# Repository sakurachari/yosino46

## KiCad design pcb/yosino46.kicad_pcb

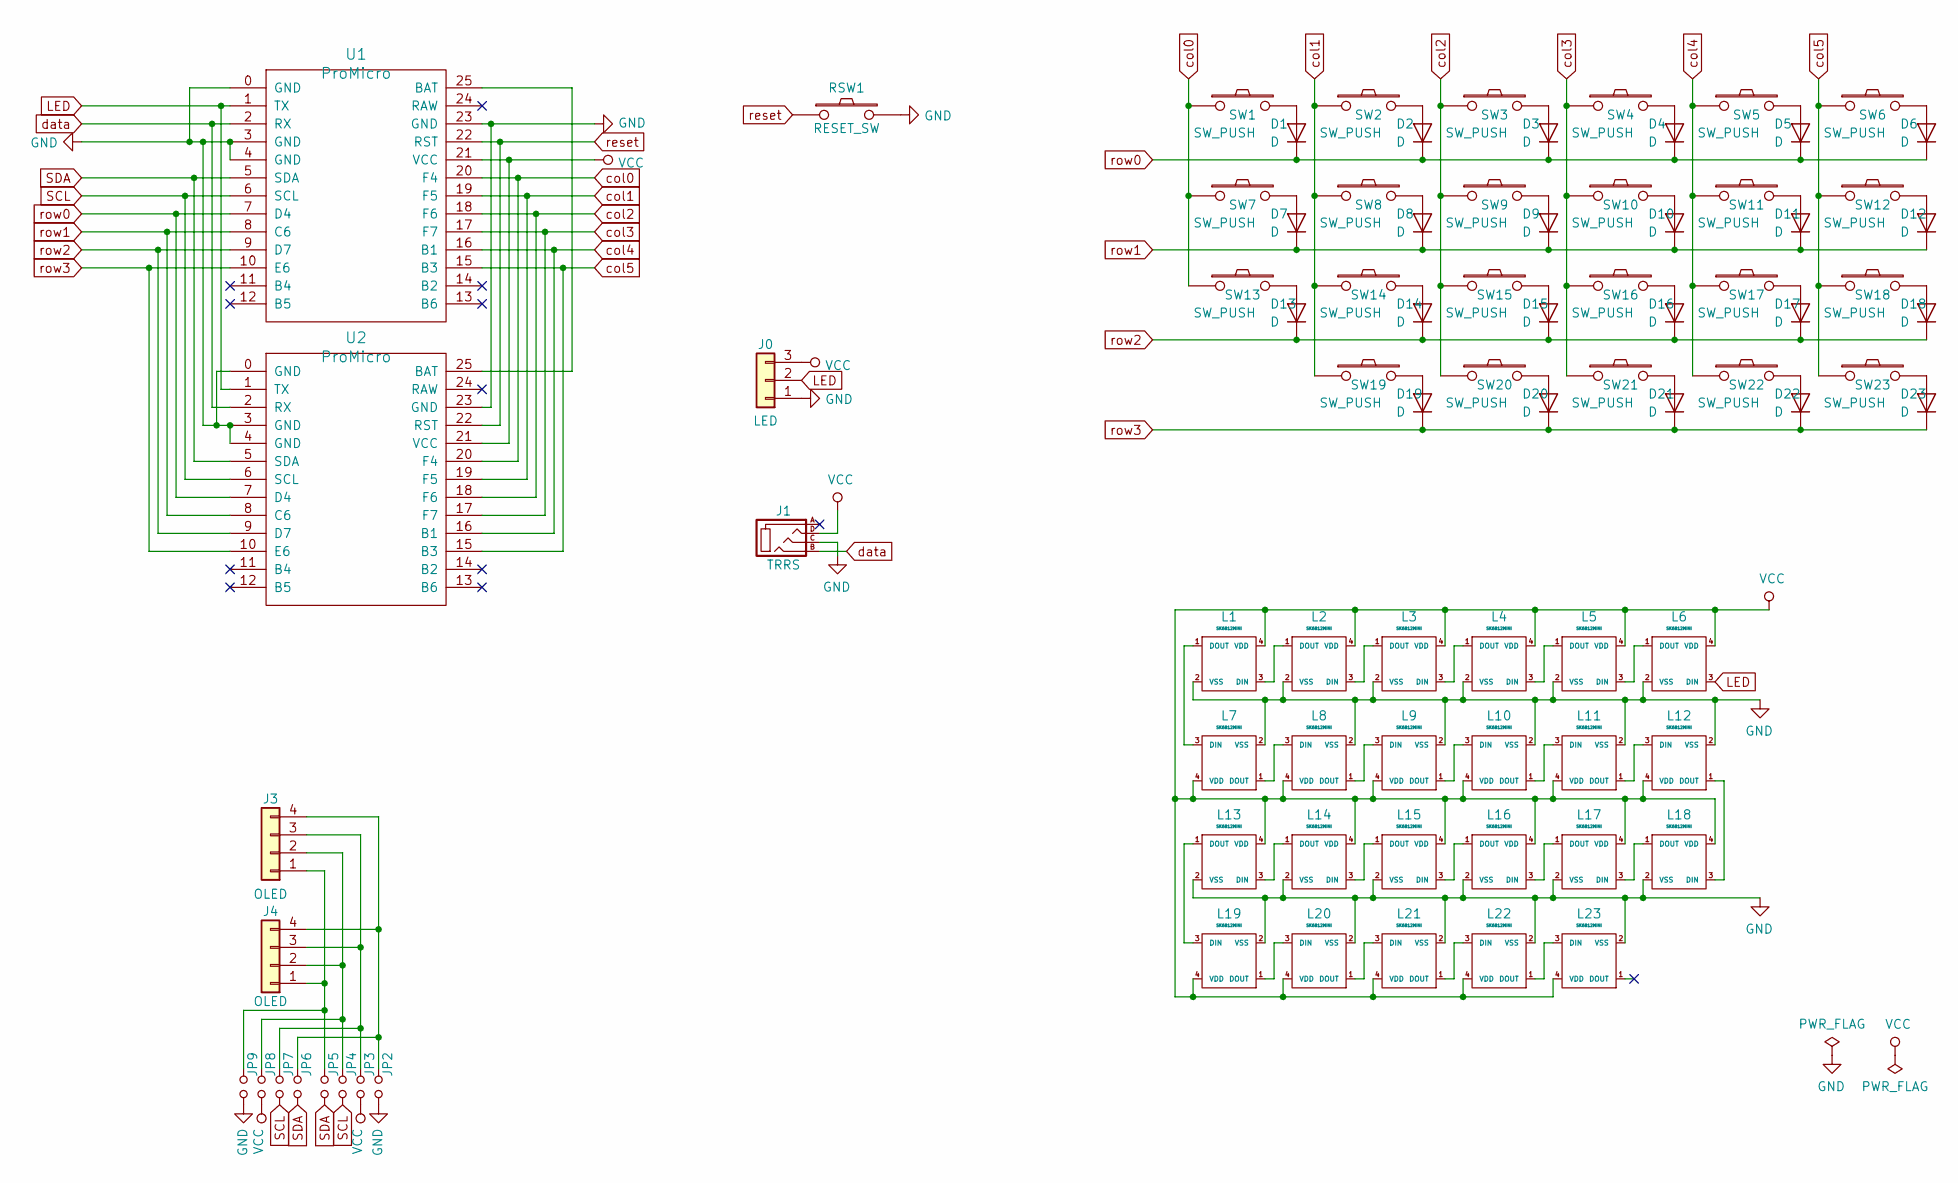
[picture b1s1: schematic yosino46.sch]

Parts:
D1, D2, D3, D4, D5, D6, D7, D8, D9, D10, D11, D12, D13, D14, D15, D16, D17, D18, D19, D20, D21, D22, D23: D; D3_TH_SMD
J0: LED; StripLED_rev
J1: TRRS; MJ-4PP-9
J3, J4: OLED
JP2, JP9: GND; Jumper
JP3, JP8: VCC; Jumper
JP4, JP7: SCL; Jumper
JP5, JP6: SDA; Jumper
L1, L2, L3, L4, L5, L6, L7, L8, L9, L10, L11, L12, L13, L14, L15, L16, L17, L18, L19, L20, L21, L22, L23: SK6812MINI; SK6812MINI_rev
RSW1: RESET_SW; ResetSW
SW1, SW2, SW3, SW4, SW5, SW6, SW7, SW8, SW9, SW10, SW11, SW12, SW13, SW14, SW15, SW16, SW17, SW18, SW19, SW20, SW21, SW22: SW_PUSH; CherryMX_Hotswap
SW23: SW_PUSH; CherryMX_Hotswap2U_stabilizer.
U1, U2: ProMicro; ProMicro_BLE

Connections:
GND: J0.1, J1.C, JP2.2, JP9.2, L1.2 (VSS), L2.2 (VSS), L3.2 (VSS), L4.2 (VSS), L5.2 (VSS), L6.2 (VSS), L7.2 (VSS), L8.2 (VSS), L9.2 (VSS), L10.2 (VSS), L11.2 (VSS), L12.2 (VSS), L13.2 (VSS), L14.2 (VSS), L15.2 (VSS), L16.2 (VSS), L17.2 (VSS), L18.2 (VSS), L19.2 (VSS), L20.2 (VSS), L21.2 (VSS), L22.2 (VSS), L23.2 (VSS), RSW1.2, U1.0 (GND), U1.3 (GND), U1.4 (GND), U1.23 (GND), U2.0 (GND), U2.3 (GND), U2.4 (GND), U2.23 (GND)
LED: J0.2, L6.3 (DIN), U1.1 (TX), U2.1 (TX)
unnamed: D1.2 (A), SW1.2
unnamed: D2.2 (A), SW2.2
unnamed: D3.2 (A), SW3.2
unnamed: D4.2 (A), SW4.2
unnamed: D5.2 (A), SW5.2
unnamed: D6.2 (A), SW6.2
unnamed: D7.2 (A), SW7.2
unnamed: D8.2 (A), SW8.2
unnamed: D9.2 (A), SW9.2
unnamed: D10.2 (A), SW10.2
unnamed: D11.2 (A), SW11.2
unnamed: D12.2 (A), SW12.2
unnamed: D13.2 (A), SW13.2
unnamed: D14.2 (A), SW14.2
unnamed: D15.2 (A), SW15.2
unnamed: D16.2 (A), SW16.2
unnamed: D17.2 (A), SW17.2
unnamed: D18.2 (A), SW18.2
unnamed: D19.2 (A), SW19.2
unnamed: D20.2 (A), SW20.2
unnamed: D21.2 (A), SW21.2
unnamed: D22.2 (A), SW22.2
unnamed: D23.2 (A), SW23.2
unnamed: J3.1, J4.1, JP5.1, JP9.1
unnamed: J3.2, J4.2, JP4.1, JP8.1
unnamed: J3.3, J4.3, JP3.1, JP7.1
unnamed: J3.4, J4.4, JP2.1, JP6.1
unnamed: L1.1 (DOUT), L7.3 (DIN)
unnamed: L1.3 (DIN), L2.1 (DOUT)
unnamed: L2.3 (DIN), L3.1 (DOUT)
unnamed: L3.3 (DIN), L4.1 (DOUT)
unnamed: L4.3 (DIN), L5.1 (DOUT)
unnamed: L5.3 (DIN), L6.1 (DOUT)
unnamed: L7.1 (DOUT), L8.3 (DIN)
unnamed: L8.1 (DOUT), L9.3 (DIN)
unnamed: L10.1 (DOUT), L11.3 (DIN)
unnamed: L9.1 (DOUT), L10.3 (DIN)
unnamed: L11.1 (DOUT), L12.3 (DIN)
unnamed: L12.1 (DOUT), L18.3 (DIN)
unnamed: L13.1 (DOUT), L19.3 (DIN)
unnamed: L13.3 (DIN), L14.1 (DOUT)
unnamed: L14.3 (DIN), L15.1 (DOUT)
unnamed: L15.3 (DIN), L16.1 (DOUT)
unnamed: L16.3 (DIN), L17.1 (DOUT)
unnamed: L17.3 (DIN), L18.1 (DOUT)
unnamed: L19.1 (DOUT), L20.3 (DIN)
unnamed: L20.1 (DOUT), L21.3 (DIN)
unnamed: L21.1 (DOUT), L22.3 (DIN)
unnamed: L22.1 (DOUT), L23.3 (DIN)
unnamed: U1.25 (BAT), U2.25 (BAT)
SCL: JP4.2, JP7.2, U1.6 (SCL), U2.6 (SCL)
SDA: JP5.2, JP6.2, U1.5 (SDA), U2.5 (SDA)
VCC: J0.3, J1.D, JP3.2, JP8.2, L1.4 (VDD), L2.4 (VDD), L3.4 (VDD), L4.4 (VDD), L5.4 (VDD), L6.4 (VDD), L7.4 (VDD), L8.4 (VDD), L9.4 (VDD), L10.4 (VDD), L11.4 (VDD), L12.4 (VDD), L13.4 (VDD), L14.4 (VDD), L15.4 (VDD), L16.4 (VDD), L17.4 (VDD), L18.4 (VDD), L19.4 (VDD), L20.4 (VDD), L21.4 (VDD), L22.4 (VDD), L23.4 (VDD), U1.21 (VCC), U2.21 (VCC)
col0: SW1.1, SW7.1, SW13.1, U1.20 (F4), U2.20 (F4)
col1: SW2.1, SW8.1, SW14.1, SW19.1, U1.19 (F5), U2.19 (F5)
col2: SW3.1, SW9.1, SW15.1, SW20.1, U1.18 (F6), U2.18 (F6)
col3: SW4.1, SW10.1, SW16.1, SW21.1, U1.17 (F7), U2.17 (F7)
col4: SW5.1, SW11.1, SW17.1, SW22.1, U1.16 (B1), U2.16 (B1)
col5: SW6.1, SW12.1, SW18.1, SW23.1, U1.15 (B3), U2.15 (B3)
data: J1.B, U1.2 (RX), U2.2 (RX)
reset: RSW1.1, U1.22 (RST), U2.22 (RST)
row0: D1.1 (K), D2.1 (K), D3.1 (K), D4.1 (K), D5.1 (K), D6.1 (K), U1.7 (D4), U2.7 (D4)
row1: D7.1 (K), D8.1 (K), D9.1 (K), D10.1 (K), D11.1 (K), D12.1 (K), U1.8 (C6), U2.8 (C6)
row2: D13.1 (K), D14.1 (K), D15.1 (K), D16.1 (K), D17.1 (K), D18.1 (K), U1.9 (D7), U2.9 (D7)
row3: D19.1 (K), D20.1 (K), D21.1 (K), D22.1 (K), D23.1 (K), U1.10 (E6), U2.10 (E6)

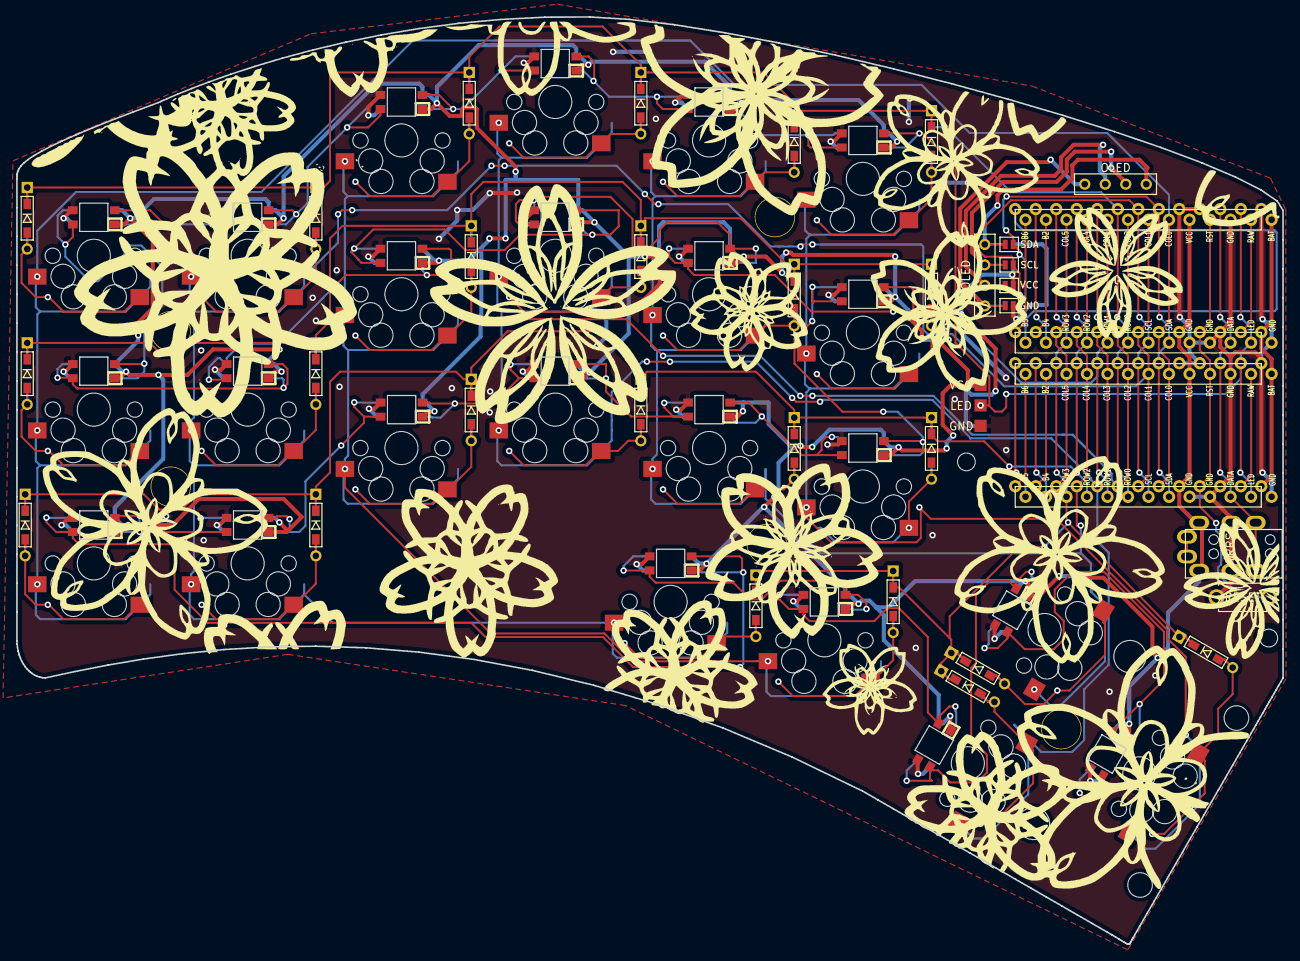
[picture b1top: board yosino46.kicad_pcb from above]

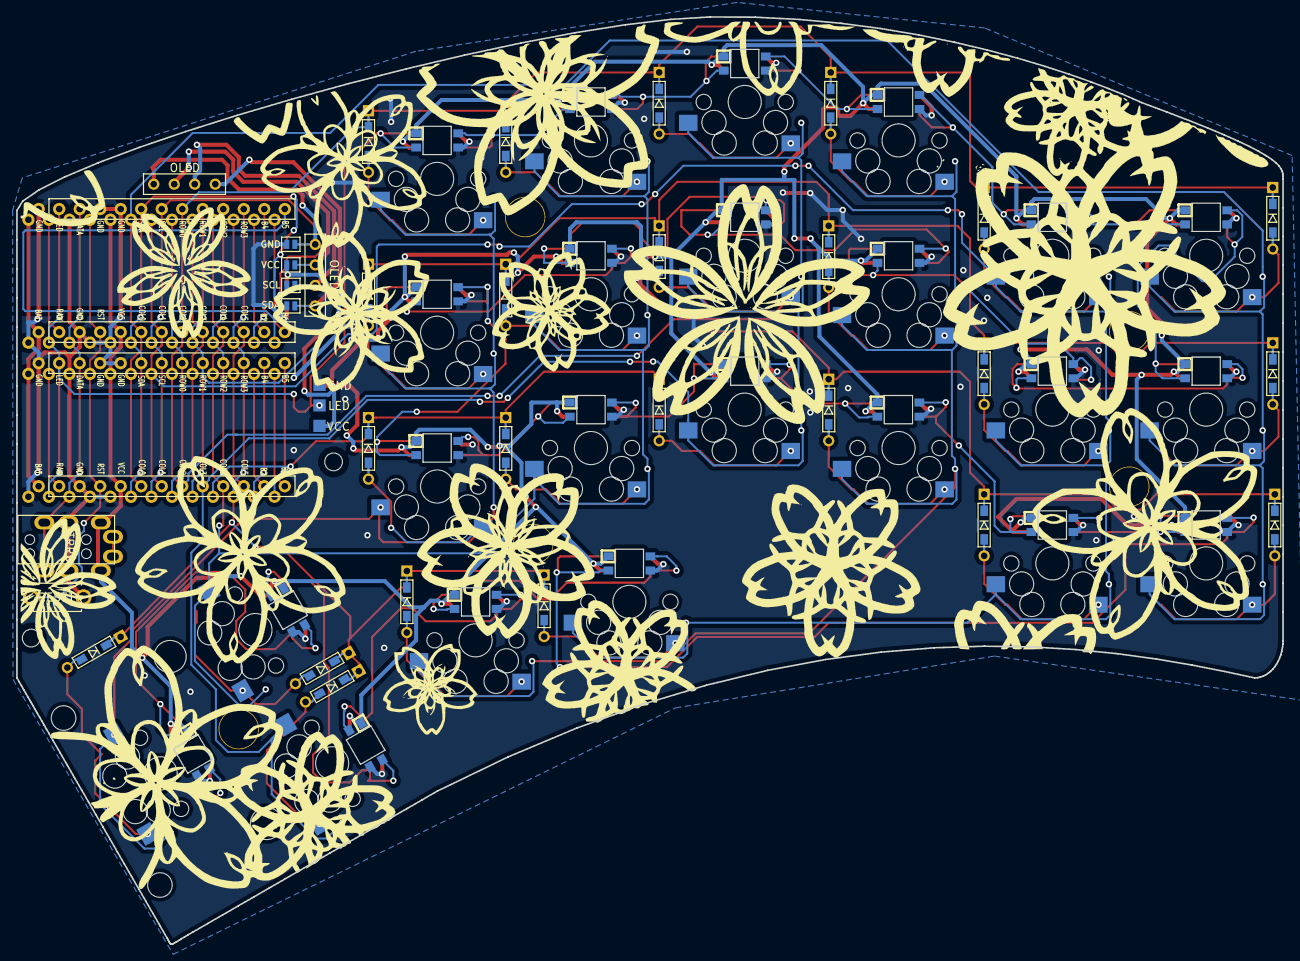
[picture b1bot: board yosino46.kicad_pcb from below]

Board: 2 copper layers, 156.8 x 114.8 mm, 91 parts (4 on the bottom side), 67 nets.

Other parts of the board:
HOLE_M2, HOLE_M2#2: VAL**; M2_HOLE
Ref**: Val**; spacer
Ref**#2, Ref**#3, Ref**#4, Ref**#5: Val**; spacer

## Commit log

2019-05-09 yosino46作成
